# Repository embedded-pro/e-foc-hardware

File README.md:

# e-foc — Hardware

A three-phase brushless (BLDC / PMSM) motor driver board designed to run the
[**e-foc** Field-Oriented Control firmware](https://github.com/embedded-pro/e-foc).

This repository contains the **KiCad** electrical design — schematics, project
configuration and (eventually) the PCB layout — for the power and signal-chain
hardware that the e-foc control software targets. The microcontroller itself
lives on a pluggable module; this board provides the power stage, gate drive,
current sensing, protection and peripheral connectivity around it.

> **Scope:** this repo is the *hardware*. For the control algorithms (Clarke/Park
> transforms, Space Vector Modulation, current/velocity PID loops, auto-tuning),
> see the [firmware repository](https://github.com/embedded-pro/e-foc).

---

## Highlights

- **Three-phase inverter** built from three TI `CSD88537ND` 60 V dual NexFET™
  half-bridge power blocks (one per phase) — low R<sub>DS(on)</sub>, sized for a
  50 V bus at 5 A.
- **`FAN7888` 3-phase gate driver** with bootstrap high-side supply for clean,
  cross-conduction-protected switching.
- **Low-side shunt current sensing** (0.02 Ω) on each phase, amplified and
  filtered through a dedicated `TLV9062` / `TLV9064` analog conditioning stage
  for the controller's ADC.
- **Wide-input switching power supply** — `LM5164` 100 V synchronous buck plus
  `AMS1117` linear regulators generating the +15 V gate-drive rail, +5 V and
  +3.3 V logic rails, with TVS bus-clamp protection (`SMCJ51A`).
- **CAN connectivity** via an `SN65HVD230` transceiver for multi-axis /
  networked control.
- **Non-volatile storage** — `24LC04` I²C EEPROM (calibration / parameters) and
  `W25Q32` 32-Mbit SPI flash (logs / firmware assets).
- **MCU-agnostic carrier** — the controller plugs in over a 24-pin (2×12)
  header, matching the firmware's `PlatformFactory` abstraction (e.g. STM32F407
  or TI Tiva TM4C1294 modules).

---

## Board architecture

The design is organised as hierarchical schematic sheets, each a self-contained
functional block:

| Sheet | Function | Key parts |
|-------|----------|-----------|
| `e-foc.kicad_sch` | Top-level sheet wiring all blocks together | — |
| `power-supply` | Wide-input supply: gate-drive + logic rails, protection | `LM5164`, `AMS1117-3.3`, `SMCJ51A` (D1 bus TVS) |
| `driver` | Three-phase inverter, gate drive, phase shunts, motor terminals | `FAN7888`, 3× `CSD88537ND`, 0.02 Ω shunts |
| `adc-conditioner` | Current/voltage sense amplification & anti-alias filtering | `TLV9062`, `TLV9064` |
| `microcontroller-connector` | 2×12 header to the MCU module + signal break-out | `Conn_02x12` |
| `can-bus` | CAN field-bus interface | `SN65HVD230` |
| `serial-com` | Serial / debug communications | — |
| `eeprom-mem` | I²C EEPROM for calibration & parameters | `24LC04` |
| `flash-mem` | SPI NOR flash for logging / assets | `W25Q32JVSS` |

---

## Design requirements (spec)

These are the **hard design targets** the board must meet — the authoritative
requirements used for design review and sign-off.

| # | Requirement | Target |
|---|-------------|--------|
| R1 | Input bus voltage | **50 V** max |
| R2 | Output current | **5 A** max continuous (DC) |
| R3 | Motor types | 3-phase brushless (BLDC) / PMSM, **FOC** control |
| R4 | PWM switching frequency | **50 kHz** max |
| R5 | Configuration storage | **EEPROM** available for parameters / calibration |
| R6 | Firmware-update storage | **External flash** for FW update |
| R7 | Field-bus | **CAN @ 1 Mbps** max, **GND present in the connector** |
| R8 | PCB stack-up | **2 layers** is sufficient |
| R9 | Position feedback | input for **encoder OR hall sensor** |

### As-built component capability

| Parameter | Value |
|-----------|-------|
| Power topology | 3× half-bridge (1 dual FET per phase), low-side shunt sensing |
| Switching devices | TI `CSD88537ND`, 60 V dual N-channel NexFET™ half-bridge (Q1–Q3) — 10 V margin over the 50 V bus (R1) |
| Bus TVS clamp | D1 = `SMCJ51A`, 51 V standoff / 1500 W (see note below) |
| Gate driver | `FAN7888`, 3-phase, bootstrap high-side |
| Current sense | 0.02 Ω low-side shunt per phase + op-amp gain stage |
| Logic rails | +3.3 V logic + gate-drive rail (FAN7888 VDD) |
| Protection | TVS bus clamp (`SMCJ51A`), CAN ESD array, gate clamps |
| Comms | CAN (`SN65HVD230`, R7), serial / debug |
| Storage | I²C EEPROM (`24LC04`, R5), SPI flash (`W25Q32`, 32 Mbit, R6) |
| Controller | External 24-pin MCU module (STM32 / TI Tiva, via firmware abstraction) |

> **D1 TVS sizing.** The bus is 50 V max; the `CSD88537ND` is a 60 V FET. A
> standard TVS cannot both stand off 50 V *and* clamp below 60 V (clamp ratio
> ~1.5×), so `SMCJ51A` (Vrwm 51 V, Vbr ≥ 56.7 V, Vc ≈ 82 V) is chosen to absorb
> gross load-dump / inductive transients without conducting in normal operation.
> The 10 V FET margin against **switching ringing** must be held by layout —
> tight commutation loop, adequate bulk capacitance, and (if needed) an RC
> snubber — not by the TVS. Compliance with R1–R9 is confirmed during design
> review and bring-up.

---

## Repository layout

```
e-foc/
├── hardware/                            # KiCad projects — one folder per board
│   ├── e-foc/                           #   main motor-driver board
│   │   ├── e-foc.kicad_pro
│   │   ├── e-foc.kicad_sch              #     top-level (root) schematic
│   │   ├── e-foc.kicad_pcb              #     PCB layout
│   │   ├── sym-lib-table
│   │   ├── components/                  #     project symbol libs (e.g. CSD88537ND)
│   │   └── schematic/                   #     hierarchical sub-sheets
│   │       ├── power-supply.kicad_sch
│   │       ├── driver.kicad_sch
│   │       └── … adc-conditioner, can-bus, encoder, eeprom-mem,
│   │             flash-mem, microcontroller-connector, serial-com
│   └── tiva-80pin-adapter/              #   EK-TM4C1294XL ↔ e-foc adapter board
│       ├── tiva-80pin-adapter.kicad_pro
│       ├── tiva-80pin-adapter.kicad_sch
│       └── tiva-80pin-adapter.kicad_pcb
├── scripts/                            # export helpers (run per board)
│   ├── export_review.py                #   review package  -> review_exports/<board>/
│   └── export_jlcpcb.py                #   fab + assembly  -> manufacturing/<board>/
└── .github/workflows/                  # CI: kicad-bot.yml (quality gate) + release.yml
```

> Each board is a self-contained KiCad project in its own `hardware/<board>/`
> folder — the `.kicad_pro`, root schematic and board share that folder (KiCad
> locates them by name and path). Hierarchical sub-sheets and project symbol libs
> are referenced by relative path within the board folder. Generated outputs are
> gitignored and land under `review_exports/<board>/` and `manufacturing/<board>/`.

---

## Getting started

This is a [**KiCad 10**](https://www.kicad.org/) project.

1. Clone the repository:
   ```bash
   git clone https://github.com/embedded-pro/e-foc-hw.git
   cd e-foc-hw
   ```
2. Open `hardware/e-foc/e-foc.kicad_pro` (or
   `hardware/tiva-80pin-adapter/tiva-80pin-adapter.kicad_pro`) in KiCad.
3. Open the schematic editor to browse the hierarchical sheets, or the PCB
   editor for the board layout.

### Headless checks (the same ones CI runs)

With KiCad 8+ installed you can run electrical / design-rule checks locally:

```bash
kicad-cli sch erc  --output erc.json --format json hardware/e-foc/e-foc.kicad_sch
kicad-cli pcb drc  --output drc.json --format json hardware/e-foc/e-foc.kicad_pcb
```

Or use the export helpers (any board): `python scripts/export_review.py` for the
e-foc board, `python scripts/export_review.py --name tiva-80pin-adapter` for the
adapter; `scripts/export_jlcpcb.py` likewise for the fab/assembly package.

---

## Continuous integration

Every push and pull request that touches a schematic or board file is checked by
[**kicad-bot**](https://github.com/embedded-pro/kicad-bot) — a CI quality gate
that wraps `kicad-cli`, KiBot, KiCost and KiDiff to run:

- **ERC / DRC verification** — electrical and design-rule checks.
- **BOM availability** — distributor stock / lifecycle (end-of-life) flags.
- **Visual diffs** — schematic & PCB change previews on pull requests.

The workflow lives in [`.github/workflows/kicad-bot.yml`](.github/workflows/kicad-bot.yml)
and uploads a `kicad-bot-output/` artifact (report, metrics, raw violation data).

> kicad-bot is a CI guardrail, **not** a substitute for design review or sign-off.

To enable distributor BOM pricing/availability, add the relevant API keys as
repository secrets (`MOUSER_KEY`, `DIGIKEY_CLIENT_ID`, `DIGIKEY_CLIENT_SECRET`).

All third-party actions are **pinned to a full commit SHA** (with the version in a
trailing comment) for supply-chain hardening.

## Releases

Releases are automated with [release-please](https://github.com/googleapis/release-please)
and driven by [Conventional Commits](https://www.conventionalcommits.org/)
(`feat:`, `fix:`, …). The flow ([`.github/workflows/release.yml`](.github/workflows/release.yml)):

1. Commits to `main` keep an open **release PR** with the next version bump and
   `CHANGELOG.md` entries.
2. Merging that PR cuts a **GitHub Release** and tag.
3. On release, kicad-bot re-runs **ERC/DRC** (gating the release on a clean
   design), resolves the **BOM**, and produces **Gerbers / drill / position**
   files. These are zipped into `e-foc-hw-<version>.zip` and attached to the
   release as a downloadable fabrication package.

Version state is tracked in [`.release-please-manifest.json`](.release-please-manifest.json);
behaviour is configured in [`release-please-config.json`](release-please-config.json).

---

## License

Released under the [MIT License](LICENSE).

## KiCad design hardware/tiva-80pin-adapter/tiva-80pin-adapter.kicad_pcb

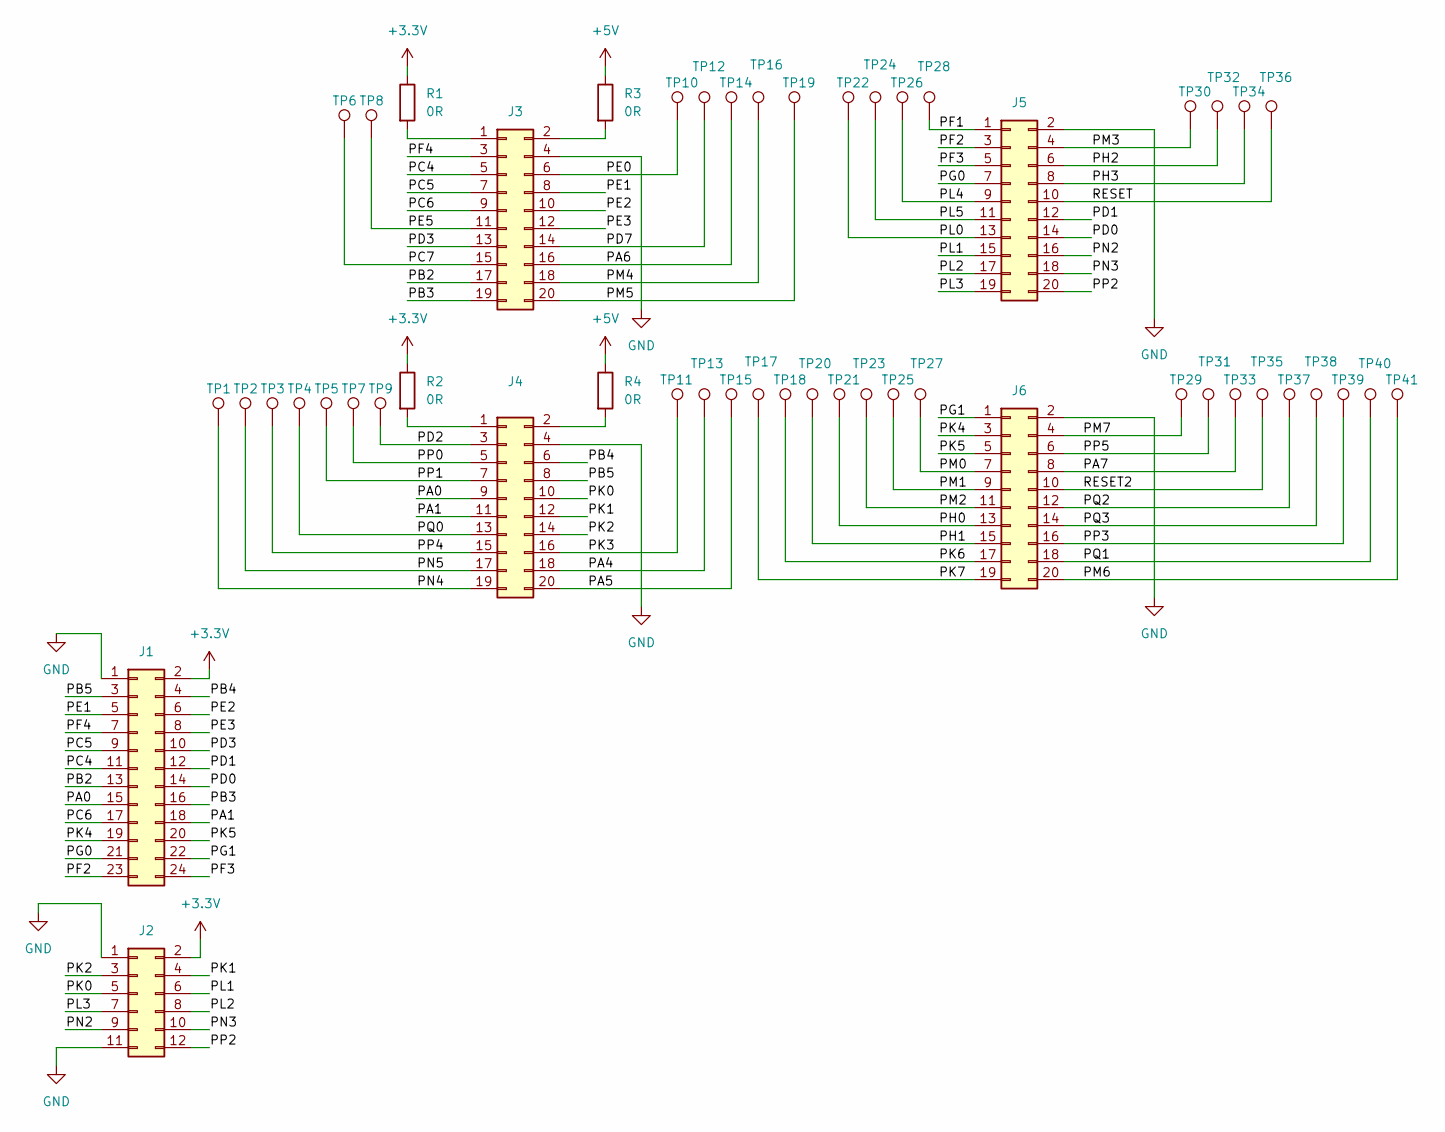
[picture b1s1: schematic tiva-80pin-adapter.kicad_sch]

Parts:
J1: Conn_02x12_Odd_Even; PinHeader_2x12_P2.54mm_Vertical
J2: Conn_02x06_Odd_Even; PinHeader_2x06_P2.54mm_Vertical
J3, J4, J5, J6: Conn_02x10_Odd_Even; PinHeader_2x10_P2.54mm_Vertical
R1, R2, R3, R4: 0R; R_0805_2012Metric_Pad1.20x1.40mm_HandSolder
TP1, TP2, TP3, TP4, TP5, TP6, TP7, TP8, TP9, TP10, TP11, TP12, TP13, TP14, TP15, TP16, TP17, TP18, TP19, TP20, TP21, TP22, TP23, TP24, TP25, TP26, TP27, TP28, TP29, TP30, TP31, TP32, TP33, TP34, TP35, TP36, TP37, TP38, TP39, TP40, TP41: TestPoint; TestPoint_Pad_D2.0mm

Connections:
+3.3V: J1.2, J2.2, R1.1, R2.1
+5V: R3.1, R4.1
/PA0: J1.15, J4.9
/PA1: J1.18, J4.11
/PA4: J4.18, TP13.1 (1_1)
/PA5: J4.20, TP15.1 (1_1)
/PA6: J3.16, TP14.1 (1_1)
/PA7: J6.8, TP33.1 (1_1)
/PB2: J1.13, J3.17
/PB3: J1.16, J3.19
/PB4: J1.4, J4.6
/PB5: J1.3, J4.8
/PC4: J1.11, J3.5
/PC5: J1.9, J3.7
/PC6: J1.17, J3.9
/PC7: J3.15, TP6.1 (1_1)
/PD0: J1.14, J5.14
/PD1: J1.12, J5.12
/PD2: J4.3, TP9.1 (1_1)
/PD3: J1.10, J3.13
/PD7: J3.14, TP12.1 (1_1)
/PE0: J3.6, TP10.1 (1_1)
/PE1: J1.5, J3.8
/PE2: J1.6, J3.10
/PE3: J1.8, J3.12
/PE5: J3.11, TP8.1 (1_1)
/PF1: J5.1, TP28.1 (1_1)
/PF2: J1.23, J5.3
/PF3: J1.24, J5.5
/PF4: J1.7, J3.3
/PG0: J1.21, J5.7
/PG1: J1.22, J6.1
/PH0: J6.13, TP21.1 (1_1)
/PH1: J6.15, TP20.1 (1_1)
/PH2: J5.6, TP32.1 (1_1)
/PH3: J5.8, TP34.1 (1_1)
/PK0: J2.5, J4.10
/PK1: J2.4, J4.12
/PK2: J2.3, J4.14
/PK3: J4.16, TP11.1 (1_1)
/PK4: J1.19, J6.3
/PK5: J1.20, J6.5
/PK6: J6.17, TP18.1 (1_1)
/PK7: J6.19, TP17.1 (1_1)
/PL0: J5.13, TP22.1 (1_1)
/PL1: J2.6, J5.15
/PL2: J2.8, J5.17
/PL3: J2.7, J5.19
/PL4: J5.9, TP26.1 (1_1)
/PL5: J5.11, TP24.1 (1_1)
/PM0: J6.7, TP27.1 (1_1)
/PM1: J6.9, TP25.1 (1_1)
/PM2: J6.11, TP23.1 (1_1)
/PM3: J5.4, TP30.1 (1_1)
/PM4: J3.18, TP16.1 (1_1)
/PM5: J3.20, TP19.1 (1_1)
/PM6: J6.20, TP41.1 (1_1)
/PM7: J6.4, TP29.1 (1_1)
/PN2: J2.9, J5.16
/PN3: J2.10, J5.18
/PN4: J4.19, TP1.1 (1_1)
/PN5: J4.17, TP2.1 (1_1)
/PP0: J4.5, TP7.1 (1_1)
/PP1: J4.7, TP5.1 (1_1)
/PP2: J2.12, J5.20
/PP3: J6.16, TP39.1 (1_1)
/PP4: J4.15, TP3.1 (1_1)
/PP5: J6.6, TP31.1 (1_1)
/PQ0: J4.13, TP4.1 (1_1)
/PQ1: J6.18, TP40.1 (1_1)
/PQ2: J6.12, TP37.1 (1_1)
/PQ3: J6.14, TP38.1 (1_1)
/RESET: J5.10, TP36.1 (1_1)
/RESET2: J6.10, TP35.1 (1_1)
GND: J1.1, J2.1, J2.11, J3.4, J4.4, J5.2, J6.2
unnamed: J3.1, R1.2
unnamed: J3.2, R3.2
unnamed: J4.1, R2.2
unnamed: J4.2, R4.2

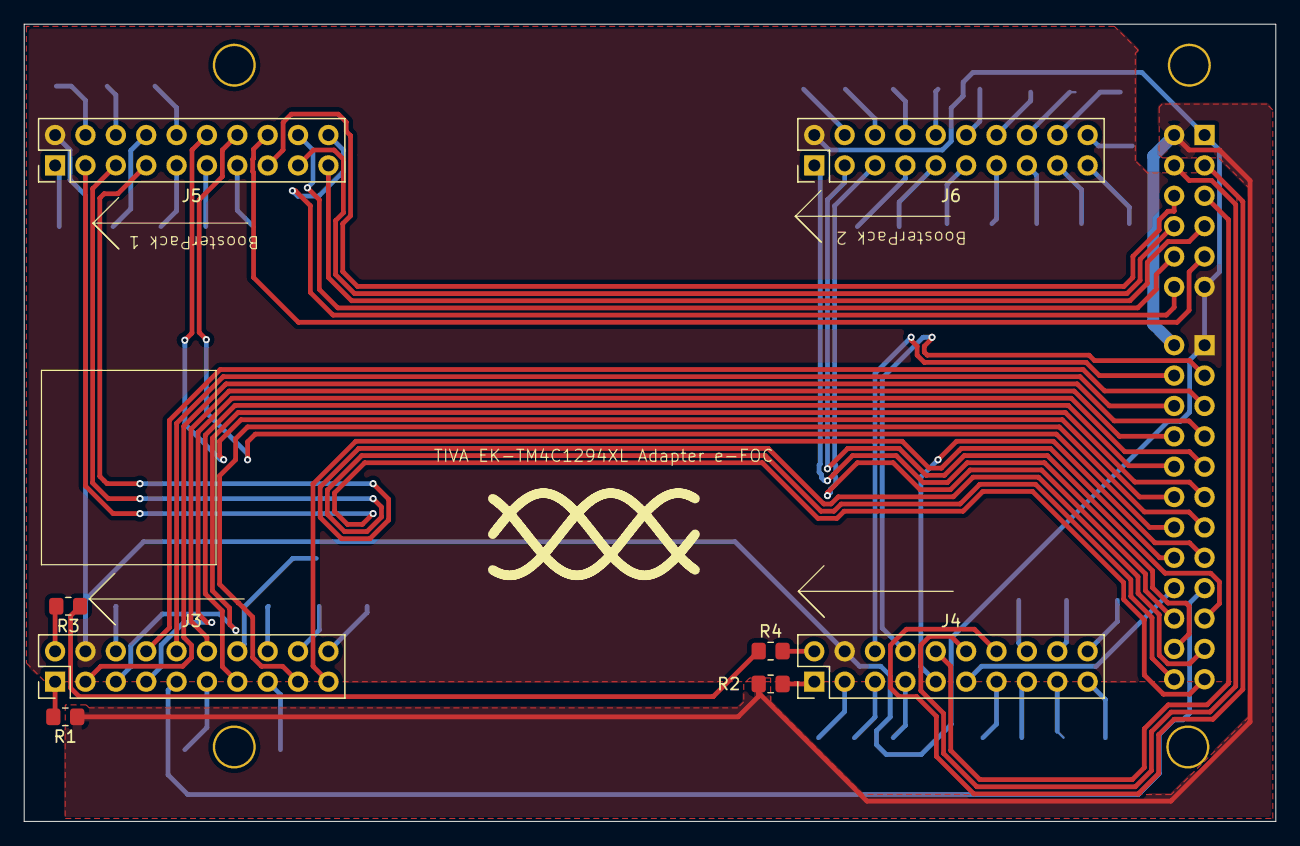
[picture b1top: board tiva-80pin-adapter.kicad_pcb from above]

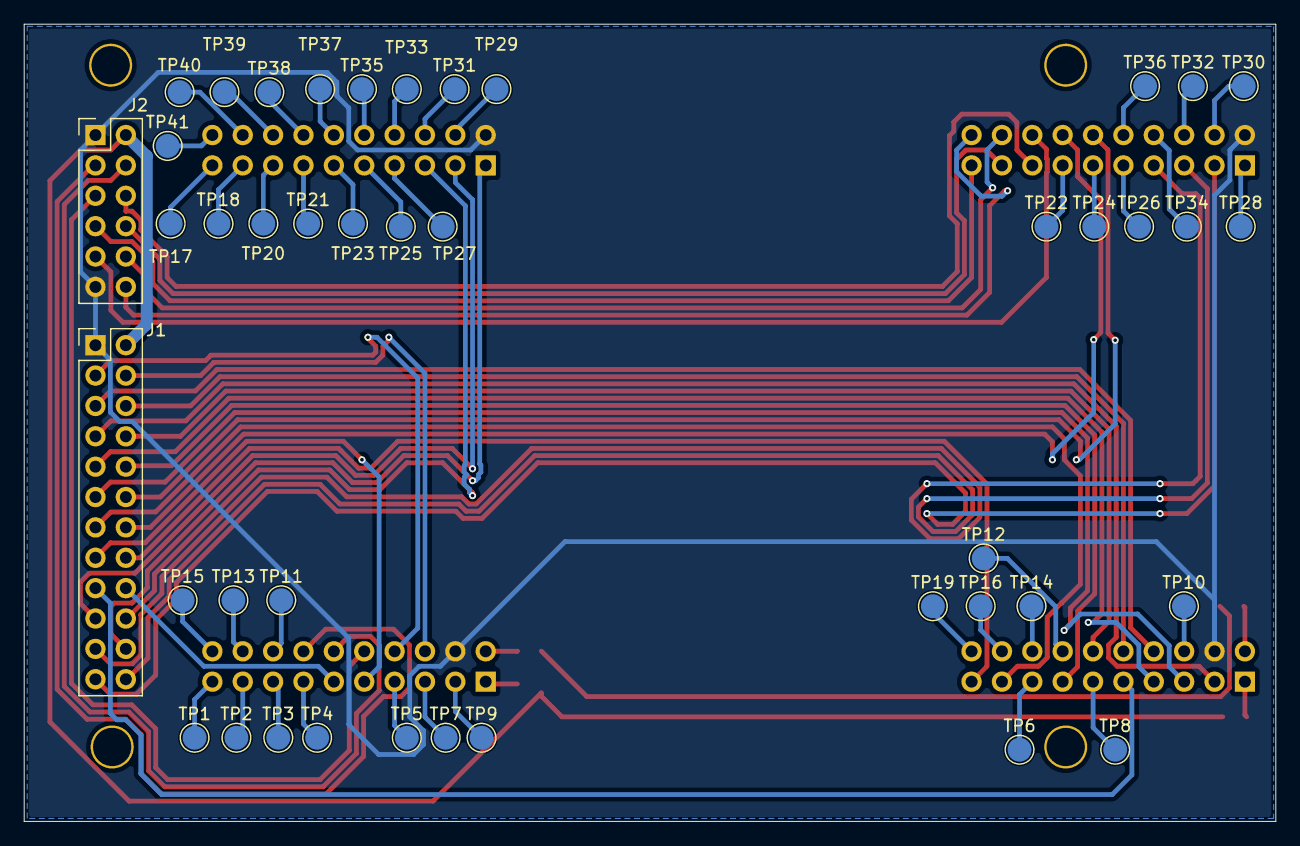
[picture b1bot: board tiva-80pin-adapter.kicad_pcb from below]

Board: 2 copper layers, 104.7 x 66.7 mm, 51 parts (43 on the bottom side), 79 nets.

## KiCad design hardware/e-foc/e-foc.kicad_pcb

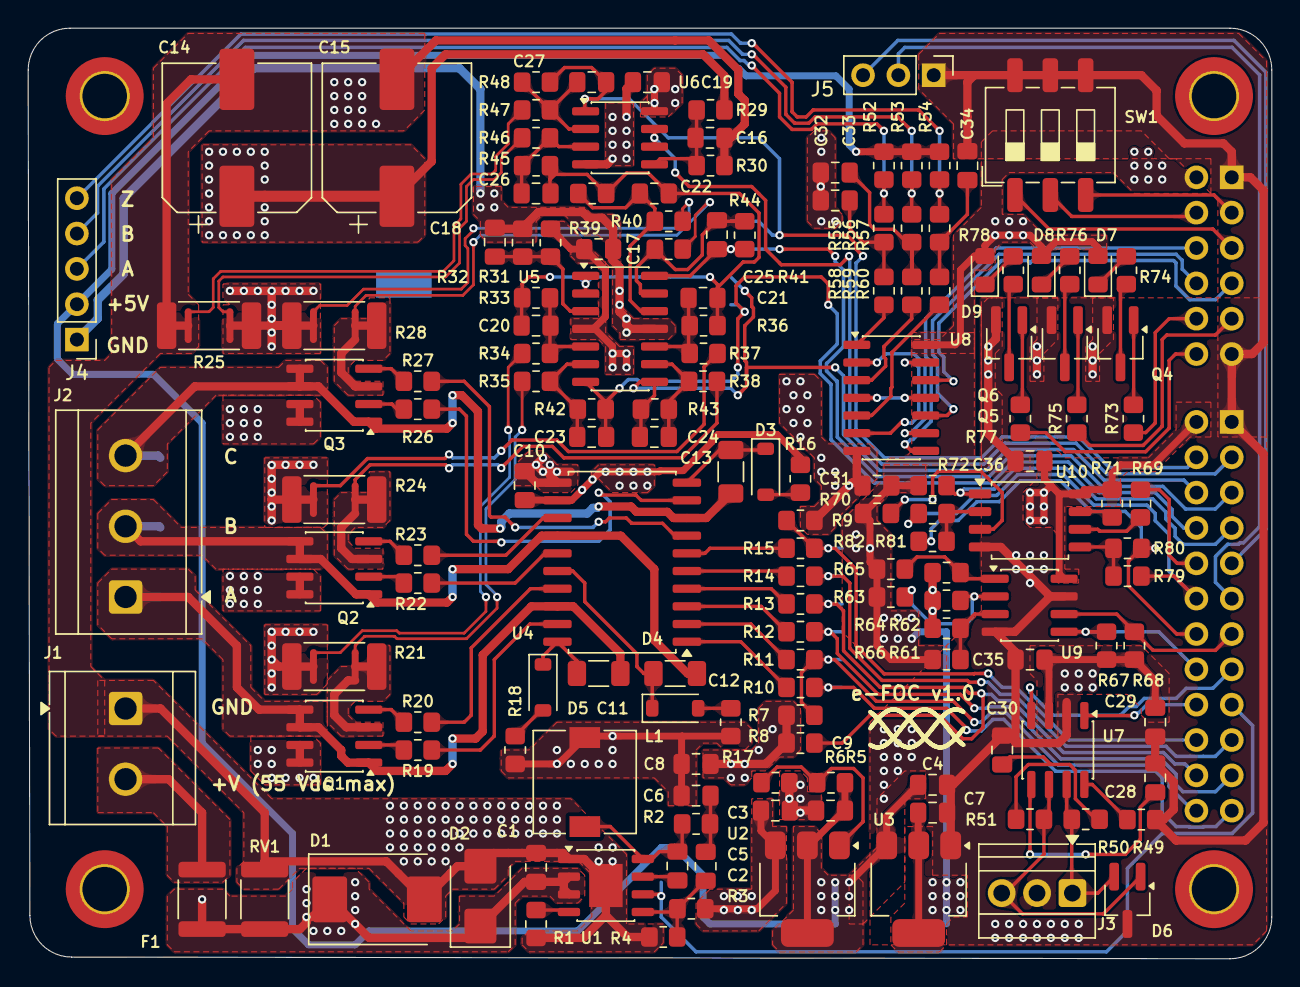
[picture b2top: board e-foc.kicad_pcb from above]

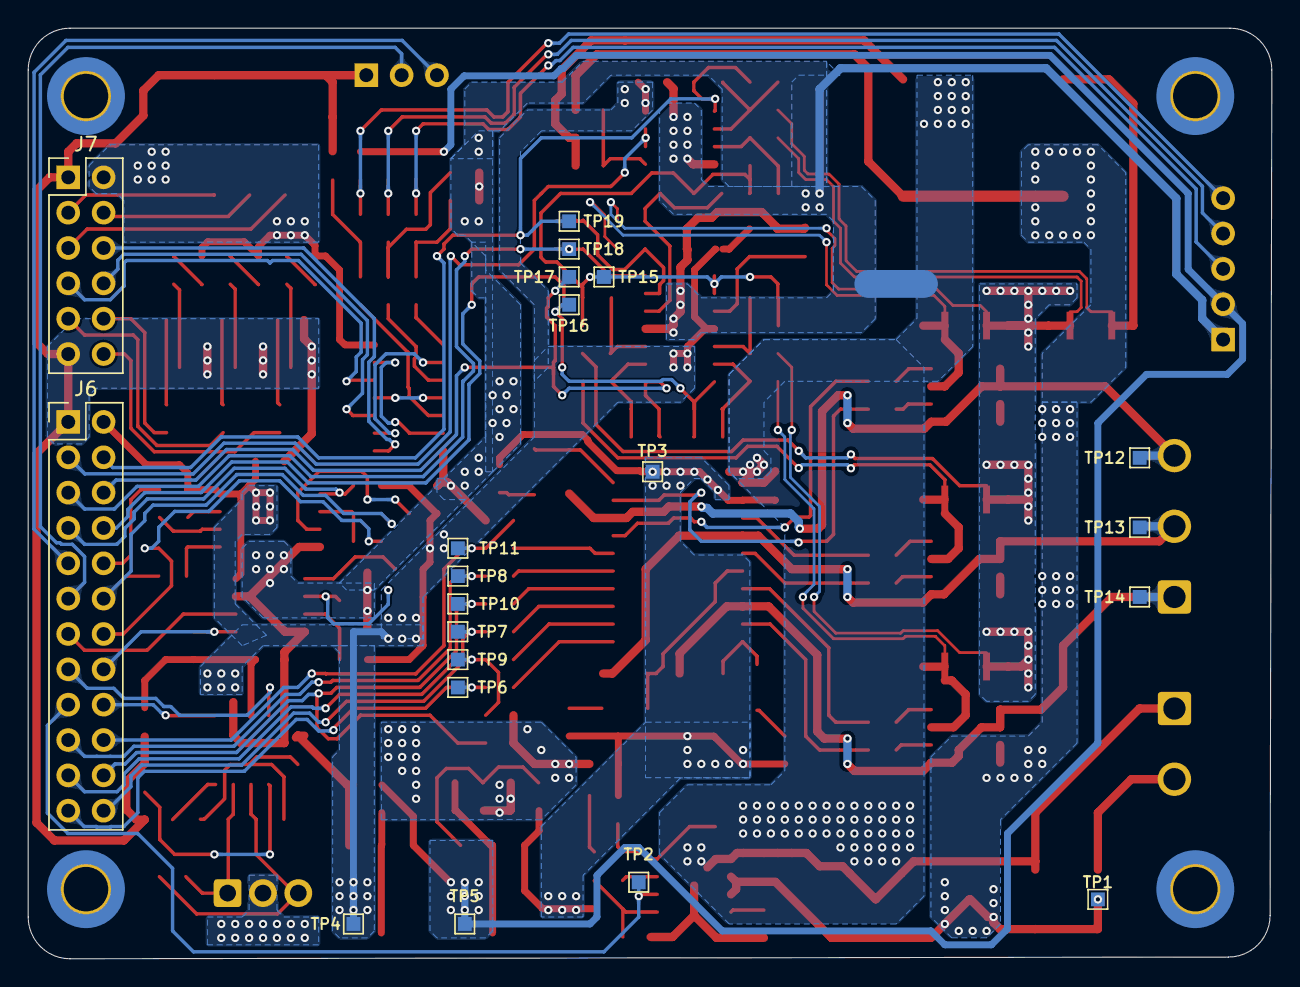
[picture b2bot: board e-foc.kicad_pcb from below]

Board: 2 copper layers, 89.4 x 66.9 mm, 186 parts (22 on the bottom side), 128 nets.

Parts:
C1: 2.2uF,100V,X7R; C_0805_2012Metric_Pad1.18x1.45mm_HandSolder
C2, C6: 2.2nF,50V,X7R; C_0805_2012Metric_Pad1.18x1.45mm_HandSolder
C3, C4, C7, C9, C10, C31: 100nF,50V,X7R; C_0805_2012Metric_Pad1.18x1.45mm_HandSolder
C5: 47pF,50V,X7R; C_0805_2012Metric_Pad1.18x1.45mm_HandSolder
C8: 4.7uF,50V,X7R; C_0805_2012Metric_Pad1.18x1.45mm_HandSolder
C11, C12, C13: 100nF,50V,X7R; C_1206_3216Metric_Pad1.33x1.80mm_HandSolder
C14, C15: 100uF/100V; CP_Elec_10x10.5
C16: 100nF,100V; C_0805_2012Metric_Pad1.18x1.45mm_HandSolder
C17, C18, C19: 100nF,16V; C_0805_2012Metric_Pad1.18x1.45mm_HandSolder
C20, C21, C22, C23, C24, C25, C26, C27: 150pF,50V; C_0805_2012Metric_Pad1.18x1.45mm_HandSolder
C28, C29, C35, C36: 100nF,16V,X7R; C_0805_2012Metric_Pad1.18x1.45mm_HandSolder
C30: 4.7nF; C_0805_2012Metric_Pad1.18x1.45mm_HandSolder
C32, C33, C34: 100pF,15V; C_0805_2012Metric_Pad1.18x1.45mm_HandSolder
D1: SMCJ51A; D_SMC
D2: 1SMB5945BT3G; D_SMB
D3, D4, D5: 1N4148W; D_SOD-123
D6: NUP2105L; SOT-23W_Handsoldering
D7, D8, D9: LED; LED_0805_2012Metric_Pad1.15x1.40mm_HandSolder
F1: Fuse; Fuse_1812_4532Metric
H1, H2, H3, H4: MountingHole; MountingHole_3.2mm_M3_DIN965_Pad_TopBottom
J1: Screw_Terminal_01x02; TerminalBlock_CUI_TB007-508-02_1x02_P5.08mm_Horizontal
J2: Screw_Terminal_01x03; TerminalBlock_CUI_TB007-508-03_1x03_P5.08mm_Horizontal
J3: Screw_Terminal_01x03; TerminalBlock_Xinya_XY308-2.54-3P_1x03_P2.54mm_Horizontal
J4: Conn_01x05_Pin; PinHeader_1x05_P2.54mm_Vertical
J5: Conn_01x03; PinHeader_1x03_P2.54mm_Vertical
J6: Conn_02x12_Odd_Even; PinHeader_2x12_P2.54mm_Vertical
J7: Conn_02x06_Odd_Even; PinHeader_2x06_P2.54mm_Vertical
L1: 100 uH; L_7.3x7.3_H4.5
NT1: NetTie_2; NetTie-2_SMD_Pad2.0mm
NT2, NT3, NT4, NT5, NT6, NT7, NT8, NT9: NetTie_3_Tee; NetTie-3_SMD_Pad0.5mm
Q1, Q2, Q3: CSD88537ND; SOIC-8_3.9x4.9mm_P1.27mm
Q4, Q5, Q6: BC847; SOT-23W_Handsoldering
R1: 124k; R_0805_2012Metric_Pad1.20x1.40mm_HandSolder
R2: 280k; R_0805_2012Metric_Pad1.20x1.40mm_HandSolder
R3: 576k; R_0805_2012Metric_Pad1.20x1.40mm_HandSolder
R4: 50k; R_0805_2012Metric_Pad1.20x1.40mm_HandSolder
R5: 33k; R_0805_2012Metric_Pad1.20x1.40mm_HandSolder
R6, R30, R31, R32: 100k; R_0805_2012Metric_Pad1.20x1.40mm_HandSolder
R7, R8, R9: 4K7; R_0805_2012Metric_Pad1.20x1.40mm_HandSolder
R10, R11, R12, R13, R14, R15, R34, R35, R37, R38, R40, R41, R46, R47, R52, R53, R54: 1k; R_0805_2012Metric_Pad1.20x1.40mm_HandSolder
R16, R17, R18: 10; R_0805_2012Metric_Pad1.20x1.40mm_HandSolder
R19, R20, R22, R23, R26, R27: 200; R_0805_2012Metric_Pad1.20x1.40mm_HandSolder
R21, R24, R25, R28: 0.02; R_2512_6332Metric_Pad1.40x3.35mm_HandSolder
R29: 2M; R_0805_2012Metric_Pad1.20x1.40mm_HandSolder
R33, R36, R39, R42, R43, R44, R45, R48, R61, R62, R63, R64, R65, R66, R67, R68, R70, R71, R72, R73, R75, R77: 10k; R_0805_2012Metric_Pad1.20x1.40mm_HandSolder
R49, R79, R80, R81, R82: 0R; R_0805_2012Metric_Pad1.20x1.40mm_HandSolder
R50, R51: 60R; R_0805_2012Metric_Pad1.20x1.40mm_HandSolder
R55, R56, R57: 100R; R_0805_2012Metric_Pad1.20x1.40mm_HandSolder
R58, R59, R60: 2k; R_0805_2012Metric_Pad1.20x1.40mm_HandSolder
R69: 22R; R_0805_2012Metric_Pad1.20x1.40mm_HandSolder
R74, R76, R78: 470R; R_0805_2012Metric_Pad1.20x1.40mm_HandSolder
RV1: Varistor; Fuse_1812_4532Metric
SW1: SW_DIP_x03; SW_DIP_SPSTx03_Slide_6.7x9.18mm_W8.61mm_P2.54mm_LowProfile
TP1, TP2, TP3, TP4, TP5, TP6, TP7, TP8, TP9, TP10, TP11, TP12, TP13, TP14, TP15, TP16, TP17, TP18, TP19: TestPoint; TestPoint_Pad_1.0x1.0mm
U1: LM5164DDA; HSOP-8-1EP_3.9x4.9mm_P1.27mm_EP2.41x3.1mm
U2: LM317_SOT-223; SOT-223-3_TabPin2
U3: AMS1117-3.3; SOT-223-3_TabPin2
U4: FAN7888; SOIC-20W_7.5x12.8mm_P1.27mm
U5: TLV9064; SOIC-14_3.9x8.7mm_P1.27mm
U6: TLV9062; SOIC-8_3.9x4.9mm_P1.27mm
U7: SN65HVD230; SOIC-8_3.9x4.9mm_P1.27mm
U8: 74LVC14; SOIC-14_3.9x8.7mm_P1.27mm
U9: 24LC04; SOIC-8_3.9x4.9mm_P1.27mm
U10: W25Q32JVSS; SOIC-8_5.3x5.3mm_P1.27mm

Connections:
+3.3V: C7.1, C17.1, C19.1, C29.1, C31.1, C35.1, C36.1, D7.2 (A), D8.2 (A), D9.2 (A), J6.2, J7.2, R31.1, R61.1, R63.1, R65.1, R67.1, R68.1, R70.2, R71.2, R72.1, TP4.1 (1_1), U3.2 (VO), U5.4 (V+), U6.8 (V+), U7.3 (VCC), U8.14 (3.3V), U9.8 (VCC), U10.8 (VCC)
+5V: C4.1, C9.1, J4.2, R5.1, R52.1, R53.1, R54.1, TP5.1 (1_1), U2.2 (VO), U3.3 (VI)
+15V: C3.1, C6.1, C8.1, C10.1, L1.2, R3.1, R16.2, R17.2, R18.2, TP3.1 (1_1), U2.3 (VI), U4.12 (VDD)
/adc-conditioner/ADC_MIDPOINT: C20.1, C21.1, C22.1, C26.1, R33.2, R36.2, R39.2, R45.2, TP15.1 (1_1), U5.1, U5.2 (-)
/adc-conditioner/CUR_A: C23.1, J6.8, R42.1, TP16.1 (1_1), U5.7
/adc-conditioner/CUR_A_N: NT3.3, R34.2
/adc-conditioner/CUR_A_P: NT2.3, R35.2
/adc-conditioner/CUR_B: C24.1, J6.6, R43.1, TP17.1 (1_1), U5.8
/adc-conditioner/CUR_B_N: NT5.3, R37.2
/adc-conditioner/CUR_C: C25.1, J6.5, R44.1, TP18.1 (1_1), U5.14
/adc-conditioner/CUR_C_N: NT9.3, R40.2
/adc-conditioner/CUR_C_P: NT8.3, R41.2
/adc-conditioner/CUR_TOTAL: C27.1, J6.4, R48.1, TP19.1 (1_1), U6.1
/adc-conditioner/CUR_TOTAL_N: NT7.3, R47.2
/adc-conditioner/CUR_TOTAL_P: NT6.3, R46.2
/adc-conditioner/CUR­_B_P: NT4.3, R38.2
/adc-conditioner/VOLT_TOTAL: J6.3, U6.6 (-), U6.7
/can-bus/CAN_RX: J6.15, U7.4 (R)
/can-bus/CAN_TX: J6.18, U7.1 (D)
/driver/HO1: R19.2, U4.19 (HO1)
/driver/HO2: R22.2, U4.15 (HO2)
/driver/HO3: R26.2, U4.9 (HO3)
/driver/LO1: R20.2, U4.17 (LO1)
/driver/LO2: R23.2, U4.13 (LO2)
/driver/LO3: R27.2, U4.7 (LO3)
/driver/PWM_A_H: J6.23, R10.2, TP6.1 (1_1)
/driver/PWM_A_L: J6.24, R7.1, R11.2, TP9.1 (1_1)
/driver/PWM_B_H: J6.21, R12.2, TP7.1 (1_1)
/driver/PWM_B_L: J6.22, R8.1, R13.2, TP10.1 (1_1)
/driver/PWM_C_H: J6.19, R14.2, TP8.1 (1_1)
/driver/PWM_C_L: J6.20, R9.1, R15.2, TP11.1 (1_1)
/driver/VS1: C11.2, J2.1, Q1.1 (S), Q1.5 (D), Q1.6 (D), TP14.1 (1_1), U4.18 (VS1)
/driver/VS2: C12.2, J2.2, Q2.1 (S), Q2.5 (D), Q2.6 (D), TP13.1 (1_1), U4.14 (VS2)
/driver/VS3: C13.2, J2.3, Q3.1 (S), Q3.5 (D), Q3.6 (D), TP12.1 (1_1), U4.8 (VS3)
/eeprom-mem/I2C_SCL: J6.13, R68.2, U9.6 (SCL)
/eeprom-mem/I2C_SDA: J6.16, R67.2, U9.5 (SDA)
/encoder/ENC_A: J7.6, U8.8
/encoder/ENC_B: J7.8, U8.10
/encoder/ENC_C: J7.7, U8.12
/flash-mem/SPI_CS: J6.7, R72.2, U10.1 (~CS)
/flash-mem/SPI_MISO: R79.2, R80.2, U10.5 (DI/IO_{0})
/flash-mem/SPI_MOSI: R81.2, R82.2, U10.2 (DO/IO_{1})
/flash-mem/SPI_SCK: J6.10, R69.2
/microcontroller-connector/BTN_1: J7.5, SW1.1
/microcontroller-connector/BTN_2: J7.4, SW1.2
/microcontroller-connector/BTN_3: J7.3, SW1.3
/microcontroller-connector/LED_B: J7.12, R77.1
/microcontroller-connector/LED_G: J7.9, R75.1
/microcontroller-connector/LED_R: J7.10, R73.1
/microcontroller-connector/POWER_GOOD: J6.17, TP2.1 (1_1), U1.6 (PGOOD)
GND: C3.2, C4.2, C7.2, C8.2, C9.2, C17.2, C18.2, C19.2, C28.2, C29.2, C30.2, C31.2, C32.2, C33.2, C34.2, C35.2, C36.2, D6.3 (A), J3.2, J4.1, J5.1, J6.1, J7.1, J7.11, NT1.1, Q4.2 (E), Q5.2 (E), Q6.2 (E), R6.2, R7.2, R8.2, R9.2, R32.2, R49.2, R62.2, R64.2, R66.2, SW1.4, SW1.5, SW1.6, U3.1 (GND), U5.11 (V-), U6.4 (V-), U7.2 (GND), U8.7 (GND), U9.4 (GND), U9.7 (WP), U10.4 (GND)
GNDPWR: C1.2, C10.2, C14.2, C15.2, C16.2, D1.2 (A2), D2.2 (A), J1.1, NT1.2, NT7.1, NT7.2, R1.2, R4.2, R25.2, R30.2, RV1.2, U1.1 (GND), U1.9 (EP), U4.11 (GND)
unnamed: C5.1, C6.2, R2.1
unnamed: C30.1, R50.2, R51.1
unnamed: C32.1, R55.1, R58.2
unnamed: C33.1, R56.1, R59.2
unnamed: C34.1, R57.1, R60.2
unnamed: D3.2 (A), R16.1
unnamed: C13.1, D3.1 (K), U4.10 (VB3)
unnamed: D4.2 (A), R17.1
unnamed: C12.1, D4.1 (K), U4.16 (VB2)
unnamed: D5.2 (A), R18.1
unnamed: C11.1, D5.1 (K), U4.20 (VB1)
unnamed: D7.1 (K), R74.2
unnamed: D8.1 (K), R76.2
unnamed: D9.1 (K), R78.2
unnamed: F1.2, J1.2
unnamed: D6.2 (K), J3.1, R50.1, U7.7 (CANH)
unnamed: D6.1 (K), J3.3, R51.2, U7.6 (CANL)
unnamed: J4.3, R52.2, R55.2
unnamed: J4.4, R53.2, R56.2
unnamed: J4.5, R54.2, R57.2
unnamed: J5.2, J6.11
unnamed: J5.3, J6.9
unnamed: J6.12, R79.1, R82.1
unnamed: J6.14, R80.1, R81.1
unnamed: NT2.1, NT2.2, Q1.3 (S), R21.1
unnamed: NT3.1, NT3.2, NT5.1, NT5.2, NT6.1, NT6.2, NT9.1, NT9.2, R21.2, R24.2, R25.1, R28.2
unnamed: NT4.1, NT4.2, Q2.3 (S), R24.1
unnamed: NT8.1, NT8.2, Q3.3 (S), R28.1
unnamed: Q1.2 (G), R19.1
unnamed: Q1.4 (G), R20.1
unnamed: Q2.2 (G), R22.1
unnamed: Q2.4 (G), R23.1
unnamed: Q3.2 (G), R26.1
unnamed: Q3.4 (G), R27.1
unnamed: Q4.1 (B), R73.2
unnamed: Q4.3 (C), R74.1
unnamed: Q5.1 (B), R75.2
unnamed: Q5.3 (C), R76.1
unnamed: Q6.1 (B), R77.2
unnamed: Q6.3 (C), R78.1
unnamed: R58.1, U8.1
unnamed: R59.1, U8.3
unnamed: R60.1, U8.5
unnamed: C2.2, U1.7 (BST)
unnamed: C5.2, R3.2, R4.1, U1.5 (FB)
unnamed: R1.1, U1.4 (RON)
unnamed: C2.1, L1.1, R2.2, U1.8 (SW)
unnamed: R5.2, R6.1, U2.1 (ADJ)
unnamed: R10.1, U4.1 (HIN1)
unnamed: R12.1, U4.3 (HIN2)
unnamed: R14.1, U4.5 (HIN3)
unnamed: R11.1, U4.2 (LIN1)
unnamed: R13.1, U4.4 (LIN2)
unnamed: R15.1, U4.6 (LIN3)
unnamed: C18.1, R31.2, R32.1, U5.3 (+)
unnamed: C20.2, R33.1, R34.1, U5.5 (+)
unnamed: C23.2, R35.1, R42.2, U5.6 (-)
unnamed: C21.2, R36.1, R37.1, U5.10 (+)
unnamed: C24.2, R38.1, R43.2, U5.9 (-)
unnamed: C22.2, R39.1, R40.1, U5.12 (+)
unnamed: C25.2, R41.1, R44.2, U5.13 (-)
unnamed: C26.2, R45.1, R46.1, U6.3 (+)
unnamed: C27.2, R47.1, R48.2, U6.2 (-)
unnamed: C16.1, R29.2, R30.1, U6.5 (+)
unnamed: R49.1, U7.8 (Rs)
unnamed: C28.1, U7.5 (Vref)
unnamed: U8.2, U8.9
unnamed: U8.4, U8.11
unnamed: U8.6, U8.13
unnamed: R65.2, R66.1, U9.1 (A0)
unnamed: R63.2, R64.1, U9.2 (A1)
unnamed: R61.2, R62.1, U9.3 (A2)
unnamed: R69.1, U10.6 (CLK)
unnamed: R71.1, U10.7 (~HOLD/~RESET/IO_{3})
unnamed: R70.1, U10.3 (~WP/IO_{2})
Vdrive: C1.1, C14.1, C15.1, D1.1 (A1), D2.1 (K), F1.1, Q1.7 (D), Q1.8 (D), Q2.7 (D), Q2.8 (D), Q3.7 (D), Q3.8 (D), R29.1, RV1.1, TP1.1 (1_1), U1.2 (VIN), U1.3 (EN/UVLO)

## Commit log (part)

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2026-06-04 add release please action
2026-06-04 refactor structure
2026-06-04 Add kicad-bot GitHub Actions workflow (v0.1.2)
2026-06-04 Pin GitHub Actions to commit SHAs instead of tags
2026-06-04 Remove paths filter so kicad-bot runs on all PRs as a gate
2026-06-06 schematic finished
2026-06-14 pcb improvements
2026-06-15 board finished
2026-06-20 .\.claude\
2026-06-21 reorganize project
2026-06-21 fix ci
2026-06-21 chore(main): release 1.0.0
2026-06-21 chore(main): release 1.0.0 (#4)
2026-06-21 docs: add component-agnostic FOC hardware design guide
    Add docs/foc-hardware-design-guide.md - an interface-style body of knowledge covering power supply, gate drive, the H-bridge power stage, over-voltage/current/temperature protection, current sensing,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
    Wire the foc-board-reviewer agent to use the guide as its rubric and knowledge base; the board README/spec stays the binding contract.
2026-06-21 docs: add component-agnostic FOC hardware design guide (#7)
    Add docs/foc-hardware-design-guide.md - an interface-style body of knowledge covering power supply, gate drive, the H-bridge power stage, over-voltage/current/temperature protection, current sensing,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
    Wire the foc-board-reviewer agent to use the guide as its rubric and knowledge base; the board README/spec stays the binding contract.
2026-06-21 chore(main): release 1.0.1

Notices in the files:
README.md:
License: MIT
